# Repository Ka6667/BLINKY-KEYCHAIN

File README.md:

## Table of Contents
* [What is BLINKY KEYCHAIN?](#what-is-blinky-keychain)
* [Why did I build it?](#why-did-i-build-it)
* [How to use BLINKY](#how-to-use-blinky)
* [How to build BLINKY](#how-to-build-blinky)
* [Schematics](#schematics)
* [PCB Design](#pcb-design)
* [BOM](#bom)

## What is BLINKY KEYCHAIN??
Blinky Keycahin is a custom made PCB that works as a keychain. it's so interactive and it looks really cool with built in modes for the LEDs. it also tells you the time in the OLED display. it's so small and so easy to assymble.

## Why did I build it?
This project is made for a friend. This friend always like to buy matching key chains so I decided to make one for both of us. The process of building was quite simple. I made the schematics using Kicad then I made the PCB. then I made a very simple zine page.

## How to use BLINKY?
the LEDS always keep making these cool patterns and the OLED Display shows the time to make sure that you will not get late to any appointment!

## How to build BLINKY?
1. First install the Gerber files and use JLCPCB to build the PCB.
2. Buy the rest of the components and use a soldering iron to solder everything.
3. Upload the code
4. ENJOY IT!!!!

## Schematics

## PCB Design

## BOM
| Part | Amount | Price | Link |
| :--- | :---: | :---: | :--- |
| XIAO-ESP32C3 | 1 | $3.9 | [Temu Link]([https://temu.com/ul/kuiper/un9.html](https://www.seeedstudio.com/XIAO-RP2040-v1-0-p-5026.html?srsltid=AfmBOorDC5QskiMPr1eQeF3IyO_gO_M0BdMRDqxPz0dwHTAT8HCzDP3a)) |
| 1000K Ohm resistor | 1 | $0.05 | [Amazon Link](https://www.amazon.eg/-/en/Resistor-1K-ohm-4W-2pcs/dp/B0CJQ3M5J1/) |
| Push-buttons | 1 | $0.04 | [Temu Link](https://www.temu.com/eg-en/10pcs-6x6x5mm--tactile-tact-push-button-micro-switch-mini-micro-momentary-tactile-push-button-switch--x-5mm-g-605681855863393.html) |
| PCB | 1 | $2.00 | [JLCPCB Link](https://cart.jlcpcb.com) |
| LED | 5 | $0.20 | [LED](https://www.ram-e-shop.com/shop/led-pack-jumbo-300-led-pack-jumbo-mixed-300-led-free-storage-box-7525?srsltid=AfmBOopEREqiHCI3qXmfFKm-uMgbiE0rt1plLX-qgW4y3SOBV-yuDqnW) |
| LIPO-Battery | 1 | $1.10 | [Makers Electronics Link](https://makerselectronics.com/product/rechargeable-400925-lipo-battery/) |
| **Total** | | **$7.3** <br>*(shipping not included)* | |

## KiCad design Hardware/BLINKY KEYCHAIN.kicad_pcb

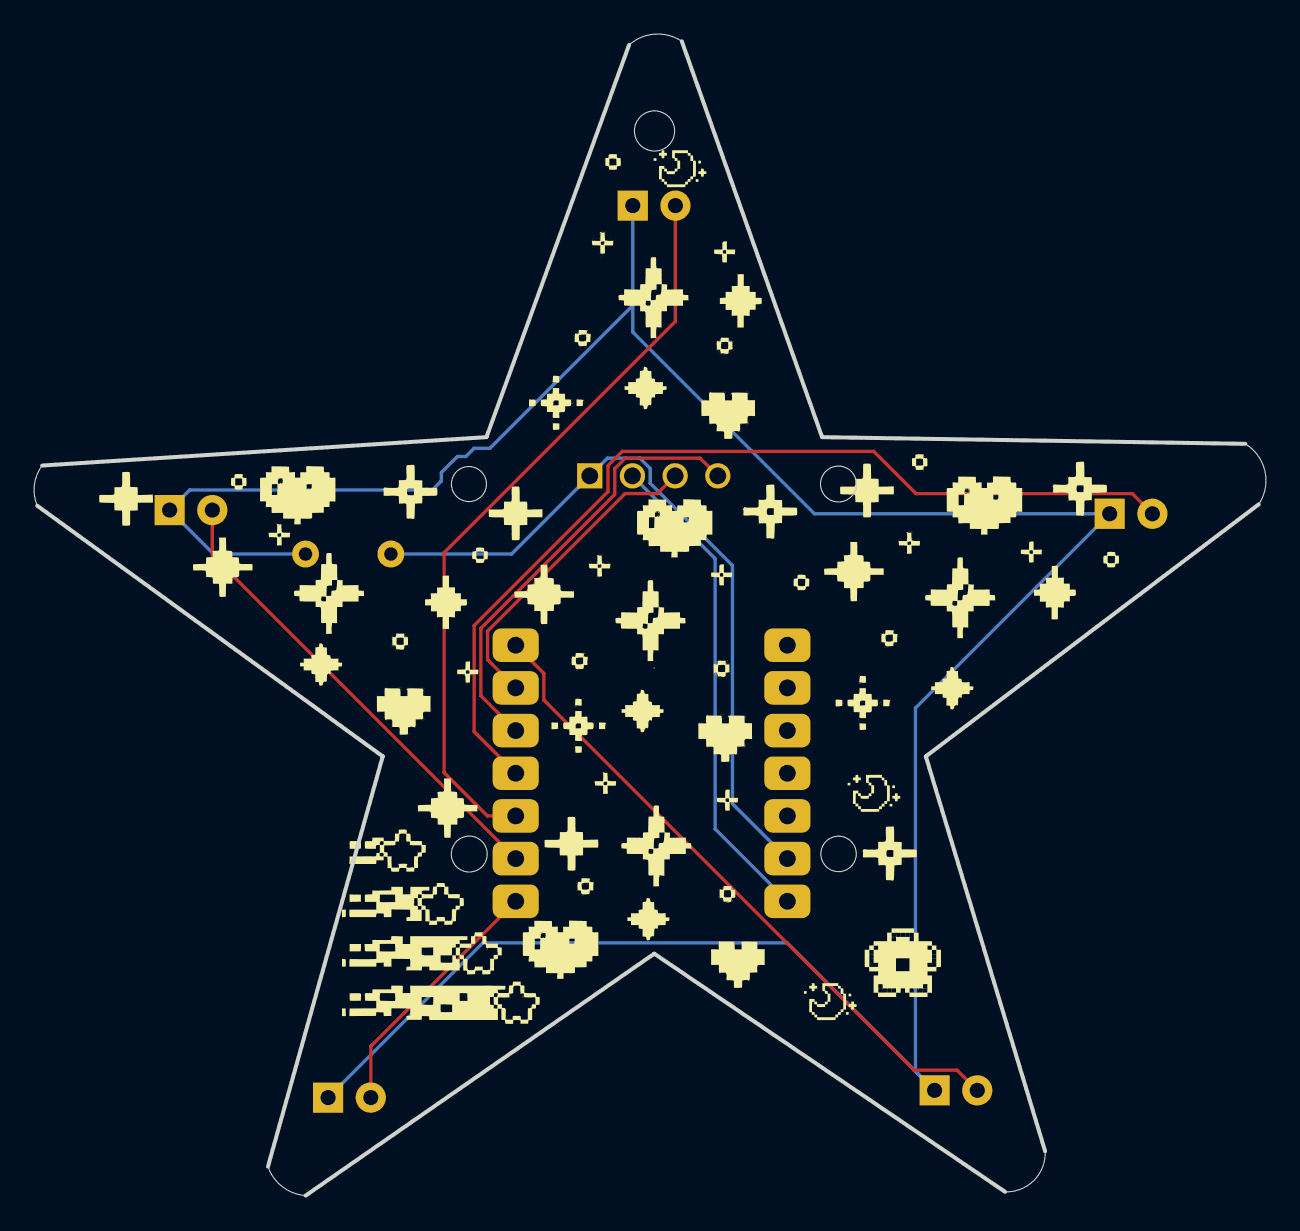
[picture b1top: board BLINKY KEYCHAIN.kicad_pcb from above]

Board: 2 copper layers, 73.3 x 69.1 mm, 8 parts (1 on the bottom side), 11 nets.

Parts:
D1, D2, D3, D4, D5: LED; LED_D3.0mm
R1: R_Small_US; R_Axial_DIN0309_L9.0mm_D3.2mm_P5.08mm_Vertical
U1: XIAO-RP2040-SMD
U2: DM-OLED096-636; MODULE_DM-OLED096-636

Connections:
+3V3: U1.12 (3V3_OUT), U1.19 (VIN)
+5V: U1.14 (VBUS), U2.2 (VCC_IN)
/D1: D1.2 (A), U1.1 (D0)
/D2: D2.2 (A), U1.2 (D1)
/D3: D3.2 (A), U1.3 (D2)
/D4: D4.2 (A), U1.4 (D3)
/D5: D5.2 (A), U1.7 (D6)
GND: R1.2, U1.13 (GND), U1.20 (GND), U2.1 (GND)
unnamed: D1.1 (K), D2.1 (K), D3.1 (K), D4.1 (K), D5.1 (K), R1.1
unnamed: U1.5 (D4), U2.4 (SDA)
unnamed: U1.6 (D5), U2.3 (SCL)
